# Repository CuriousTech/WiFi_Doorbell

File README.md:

# WiFi Doorbell Chime

This is a very small doorbell chime based closely on the older version for displaying weather and sending notifications, but eliminates the old mechanical chime. The additional parts are a MOSFET to produce PWM sound, a resistor to eliminate the chime coil and allow parasitic power to supply a smart doorbell or button light, and a WS2812B LED ring, but is still compatible with the old project. The resistor should be about 100 ohms to allow power to the smart doorbell, but I don't know the current rating for them all. A 5W should be sufficient. It's connected to the transformer while the button is pressed, so it needs to handle the current for that time.  
  
Simple operation for detection: The way this circuit operates is when the button is pressed, the optocoupler is disalbled (parrallel to the light in the button), causing the GPIO port (with internal pullup) to go low. The optocoupler vf is 1.2V up to 50mA, but works at 10mA or maybe less. The limiting resistor value will be different for 12V or 24V, so use the proper value. 1K-1K2 is fine for 12V, 2K2-2K4 should be good for 24V, and likely works for 12V as well.  
  
The 3D printed parts have 2 options: A plastic grill or a retainer ring to wrap cloth around and glue. I prefer the latter. The diffuser ring is printed in clear.  

The OLED version back with 433MHz receiver behind OLED display (cut a bit of plastic) for Reolink video doorbell RF433 output, which works the same as a standard keyfob.  

Previous version below.  

This is an ESP07 based doorbell notifier.  

The 3 terminals connect to the existing 12~24VAC (up to 40V) transformer used to power the bell solenoids and light the neon bulb in the button.  

Btn-DB connects to the wire coming from the button and connects to the bell.<br/>
Btn-TF is the one with a wire cap between the transformer and button.  <br/>
TF-DB is the one coming from the transformer and connects to the bell.<br/>

This uses PushBullet for notifications, which can be enabled from the control page as well as a short list of ring times and last PIR motion trigger time.  It also uses ESPAsyncWebServer for pages, events, WebSockets, Weather Underground, PushBullet and the AP config.  

Wunderground is used for forcast and weather alerts.  If the OLED is truned off, it will only turn on for flashing a bell icon with time, when the PIR motion sensor is triggered (doorbell times will clear after it times out), or a weather alert is active. If the OLED is on, it will show a current condition icon, and scroll the date, time and condition text unless an alert is active.  The doorbell count bar also flashes.  

There's also analog and a few more raw I/O pins broken out for more sensors or controls.  The regulator is 400mA max so it has a bit of room for expansion.  The PIR sensor is supposed to be 5V, but there was a diode and 3V3 regulator that was removed to get it to work with this.  

The web page.

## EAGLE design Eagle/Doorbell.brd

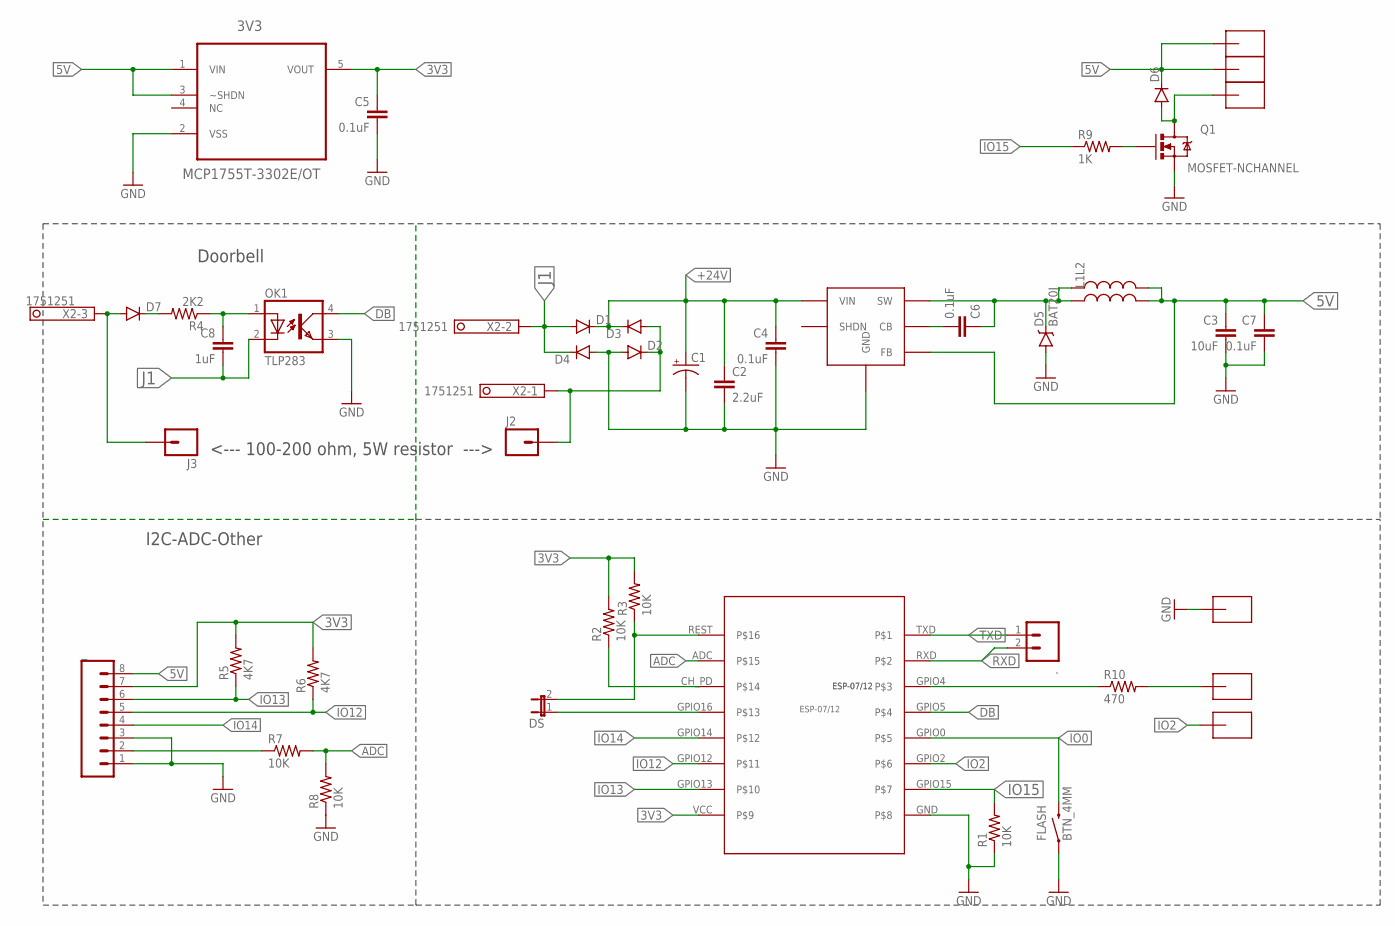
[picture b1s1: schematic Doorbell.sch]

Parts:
3V3: MCP1755T-3302E/OT; SOT95P270X145-5N
.: M02PTH; 1X02
C1: CAP_POLPTH4; CPOL-RADIAL-1000UF-25V
C2: 2.2uF; 1206
C3: 10uF; 0805-CAP
C4, C5, C6, C7: 0.1uF; 0805-CAP
C8: 1uF; 0805-CAP
D1, D2, D3, D4, D6, D7: DIODESOD123; SOD-123
D5: BAT20J; SOD-323
DS: JUMPER-2SMD-NO; SJ_2S-NO
FLASH: BTN_4MM
J2, J3: M01SMDNS; 1X01NS
L1, L2: INDUCTOR0805; 0805
OK1: TLP283; MINI-FLAT-4
Q1: MOSFET-NCHANNEL; SOT23-3
R1, R2, R3, R7, R8: 10K; 0805
R4: 2K2; 0805
R5, R6: 4K7; 0805
R9: 1K; 0805
R10: 470; 0805
U$1: ESP-07/12
U$2, U$3, U$4, U$5, U$6, U$7: SMD-PAD-SM; SMD-PAD3
VREG: LMR16006YQ5DDCRQ1; SOT-23-6
X2: 1751251
_: M08SILK_FEMALE_PTH; 1X08

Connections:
3V3: 3V3.5 (VOUT), C5.1, R2.2, R3.2, R5.2, R6.2, U$1.VCC, _.7
5V: 3V3.1 (VIN), 3V3.3 (~SHDN), C3.1, C7.1, D6.C, L1.2, L2.2, U$3.P$1, U$7.P$1, VREG.3 (FB), _.8
+24V: C1.+, C2.1, C4.1, D1.C, D3.C, VREG.5 (VIN)
ADC: R7.2, R8.2, U$1.ADC
DB: OK1.4 (COL), U$1.GPIO5
GND: 3V3.2 (VSS), C1.-, C2.2, C3.2, C4.2, C5.2, C7.2, D2.A, D4.A, D5.A, FLASH.1, OK1.3 (EMIT), Q1.2 (S), R1.1, R8.1, U$1.GND, U$4.P$1, VREG.2 (GND), _.1, _.3
ICSPCLK: DS.2, R3.1, U$1.REST
IO0: FLASH.2, U$1.GPIO0
IO2: U$1.GPIO2, U$5.P$1
IO12: R6.1, U$1.GPIO12, _.5
IO13: R5.1, U$1.GPIO13, _.6
IO14: U$1.GPIO14, _.4
IO15: R1.2, R9.1, U$1.GPIO15
IO16: DS.1, U$1.GPIO16
J1: C8.2, D1.A, D4.C, OK1.2 (C), X2.2
unnamed: D6.A, Q1.3 (D), U$6.P$1
unnamed: C8.1, OK1.1 (A), R4.1
unnamed: D2.C, D3.A, J2.1, X2.1
unnamed: R7.1, _.2
unnamed: D7.A, J3.1, X2.3
unnamed: R10.1, U$1.GPIO4
unnamed: C6.1, D5.C, L1.1, L2.1, VREG.6 (SW)
unnamed: Q1.1 (G), R9.2
unnamed: C6.2, VREG.1 (CB)
unnamed: R2.1, U$1.CH_PD
unnamed: R10.2, U$2.P$1
unnamed: D7.C, R4.2
RXD: ..2, U$1.RXD
TXD: ..1, U$1.TXD

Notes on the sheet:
I2C-ADC-Other
Doorbell
<--- 100-200 ohm, 5W resistor --->

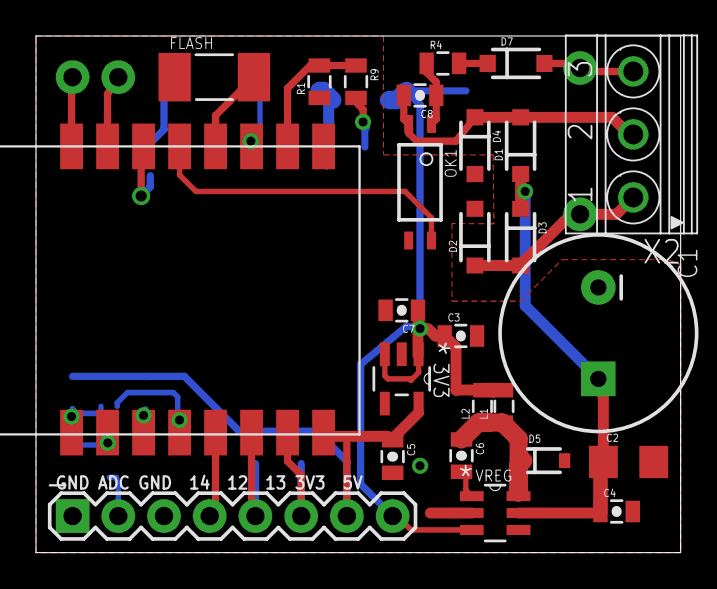
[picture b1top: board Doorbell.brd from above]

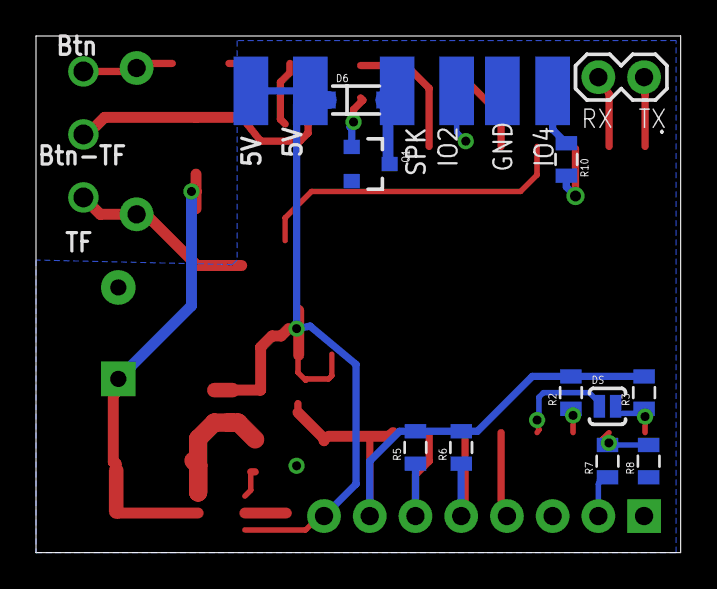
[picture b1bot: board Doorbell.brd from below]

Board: 2 copper layers, 35.8 x 28.7 mm, 45 parts (17 on the bottom side), 29 nets.

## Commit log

2016-06-10 Rename Libraries/font.h to Libraries/ssd1306_i2c/font.h
2016-06-10 Rename Libraries/icons.h to Libraries/ssd1306_i2c/icons.h
2016-06-10 Rename Libraries/keywords.txt to Libraries/ssd1306_i2c/keywords.txt
2016-06-10 Rename Libraries/ssd1306_i2c.cpp to Libraries/ssd1306_i2c/ssd1306_i2c.cpp
2016-06-10 Rename Libraries/ssd1306_i2c.h to Libraries/ssd1306_i2c/ssd1306_i2c.h
2016-06-19 Added PIR code
2016-06-19 Updated page design
2016-06-19 Push updates done
2016-06-21 More secure, alerts fixed, etc.
2016-06-23 r1 - switching supply
2016-06-25 Changed password check, added weather alert event
2016-06-27 Rebuild for JsonClient changes
2016-06-29 PIR is used for display enable now
2016-07-09 More icons
2016-07-09 Added alert icons
2016-07-14 Added a pic.
2016-07-22 fixed buffer overrun on alert message cnv
2016-07-22 Added another icon
2016-09-23 ESPAsyncTCP PushBullet lib
2016-09-23 ESPAsyncTCP SSL PushBullet lib
2016-09-23 Switched to ESPAsyncWebServer
2016-09-24 Moved EEPROM code
2016-09-24 Fixed remoteIP
2016-10-15 Added WebSockets
2016-11-05 Just date format changes
2016-11-05 Cutting down code size
2016-11-05 Async WebServer
2016-12-01 auto display on from motion
2016-12-16 Added temp/rh, weather, alert, wind
2016-12-16 Added page weather info, exploit logger, WiFi scan
2016-12-16 New webpage layout
2016-12-16 Weather alert window
2016-12-16 Status monitor, event listener, access logger
2017-01-13 Broke SSID list and change key
2017-01-13 A few minor changes
2017-03-13 weather/alert logic fix, OTA
2017-07-06 Fix for printfAll
2017-09-21 3D printed faceplate
2018-04-21 Added favicon
2018-04-21 Commented out unused icons
2018-04-21 Added notify URL
2018-04-21 Alert clear fix, extra push to URL
2018-05-01 Removed printf
2018-11-18 Semi recursive
2018-11-18 Changed to openweathermap API
2021-07-21 Added chunked write for lower delays
2021-07-21 Added test dropdowns
2021-07-22 Switched to FastLED
2021-07-22 Switched to FastLED for stability
2021-07-22 analogWriteFreq(0) crashes. Workaround added
2021-07-26 Added the inline diode
2021-07-27 Larger space for Geekcreit 0.96 OLED module
2021-09-15 Brightness control
2021-09-15 Different songs I think
2021-09-15 Added brightness per effect
2021-09-15 Non-blocking connection
2021-09-15 Too many changes
2021-09-20 OLED display issues when connecting
2021-09-20 Just a little cleaner
2021-10-03 Eliminates powerup ring
2023-01-26 Delete WiFiManager.cpp
    Switched to SmartConnect
2023-01-26 Update Doorbell.ino
    Switched to EspTouch/SmartConnect
2023-01-26 C++17 compliant
2023-02-03 Removed prefix label
2023-02-03 Removed prefix and cmd list array
2023-02-03 Updated for new jsonParse lib
2023-03-20 Forgot to remove an item in the json lists
2024-07-21 Added image
2024-07-21 Added Reolink rx
2024-07-21 Removed PIR
2024-07-23 Added autoset RF code

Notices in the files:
parts and their libraries:
SparkFun-Connectors: Licensing: Creative Commons ShareAlike 4.0 International - https://creativecommons.org/licenses/by-sa/4.0
